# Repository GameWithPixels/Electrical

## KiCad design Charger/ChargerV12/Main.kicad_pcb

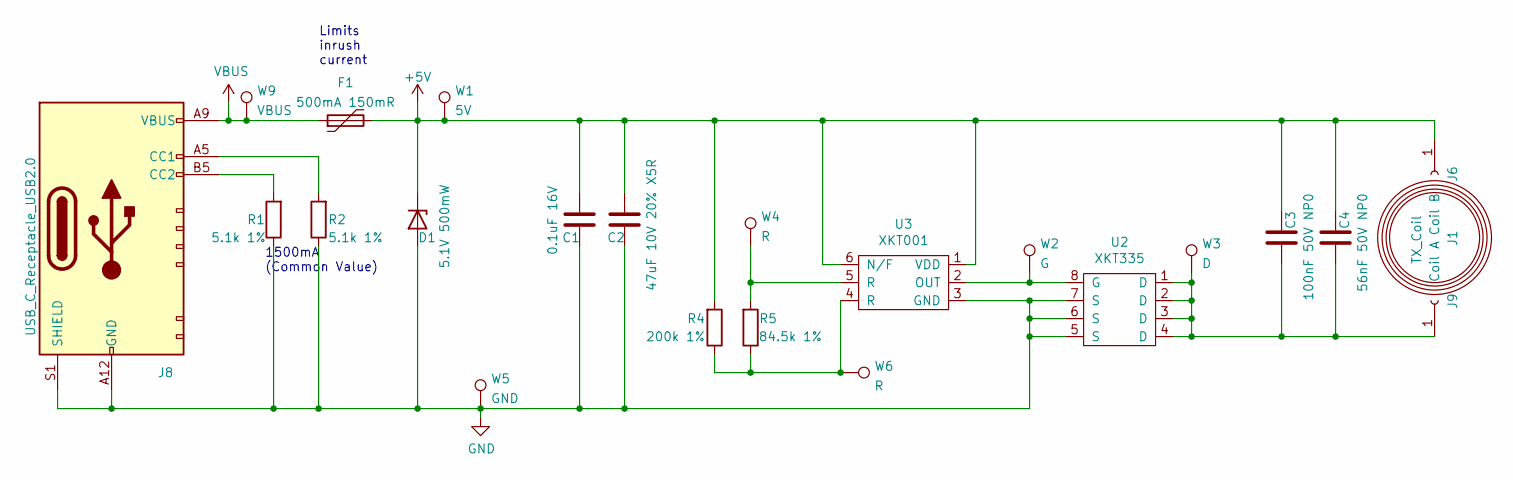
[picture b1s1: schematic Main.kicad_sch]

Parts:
C1: 0.1uF 16V; C_0603_1608Metric; Part Number CL10B104KO8NNNC; LCSC Part Number C66501
C2: 47uF 10V 20% X5R; C_1206_3216Metric; Part Number GRM31CR61A476ME15L; LCSC Part Number C94034
C3: 100nF 50V NP0; C_1206_3216Metric; Part Number GRM31C5C1H104JA01L; LCSC Part Number C21812
C4: 56nF 50V NP0; C_1206_3216Metric; Part Number GRM31M5C1H563JA01L; LCSC Part Number C441752
D1: 5.1V 500mW; D_SOD-123; Part Number BZT52C5V1; LCSC Part Number C353516
F1: 500mA 150mR; Fuse_0805_2012Metric; Part Number ASMD0805-050; LCSC Part Number C135329
J1: TX_Coil; TX Coil
J6: Coil B; TestPoint_THTPad_D2.0mm_Drill1.0mm
J8: USB_C_Receptacle_USB2.0; USB-C-SMD_10P-P1.00-L6.8-W8.9; Part Number TYPE-C-31-M-17; LCSC Part Number C283540
J9: Coil A; TestPoint_THTPad_D2.0mm_Drill1.0mm
R1, R2: 5.1k 1%; R_0402_1005Metric; Part Number 0402WGF5101TCE; LCSC Part Number C25905
R4: 200k 1%; R_0603_1608Metric; Part Number 0603WAF2003T5E; LCSC Part Number C25811
R5: 84.5k 1%; R_0603_1608Metric; Part Number 0603WAF8452T5E; LCSC Part Number C23118
U2: XKT335; SOIC-8_3.9x4.9mm_P1.27mm; Part Number XKT335
U3: XKT001; SOT-23-6; Part Number XKT001
W1: 5V; TEST_PIN
W2: G; TEST_PIN
W3: D; TEST_PIN
W4, W6: R; TEST_PIN
W5: GND; TEST_PIN
W9: VBUS; TEST_PIN

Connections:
+5V: C1.1, C2.1, C3.2, C4.2, D1.1 (K), F1.2, J6.1, R4.2, U3.1 (VDD), U3.6 (N/F), W1.1
GND: C1.2, C2.2, D1.2 (A), J8.A12 (GND), J8.B12 (GND), J8.S1 (SHIELD), R1.1, R2.1, U2.5 (S), U2.6 (S), U2.7 (S), U3.3 (GND), W5.1
unnamed: C3.1, C4.1, J9.1, U2.1 (D), U2.2 (D), U2.3 (D), U2.4 (D), W3.1
unnamed: J8.A5 (CC1), R2.2
unnamed: J8.B5 (CC2), R1.2
unnamed: R4.1, R5.1, U3.4 (R), W6.1
unnamed: R5.2, U3.5 (R), W4.1
unnamed: U2.8 (G), U3.2 (OUT), W2.1
VBUS: F1.1, J8.A9 (VBUS), J8.B9 (VBUS), W9.1

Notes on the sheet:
Limits inrush current
1500mA (Common Value)

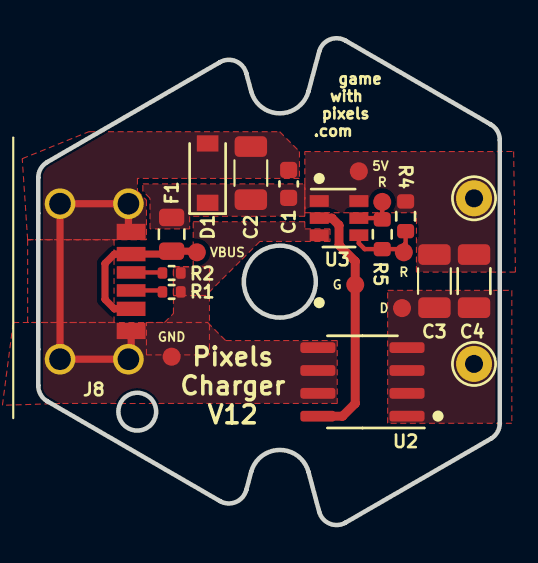
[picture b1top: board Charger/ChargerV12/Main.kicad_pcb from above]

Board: 2 copper layers, 25.6 x 27.0 mm, 23 parts (1 on the bottom side), 9 nets.

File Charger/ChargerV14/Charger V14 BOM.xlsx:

Source: | C:\Projects\Pixels-dice\Electrical\Charger\ChargerV14\Main.kicad_sch
Date: | 44894.778726851851
Item | Qty | Reference(s) | Value | Footprint | Manufacturer | Part Number
1 | 1 | C1 | 0.1uF 16V | Capacitor_SMD:C_0603_1608Metric | Samsung Electro-Mechanics | CL10B104KO8NNNC
2 | 1 | C2 | 100uF 10V 20% X5R | Capacitor_SMD:C_1206_3216Metric | Murata | GRM31CR61A107MEA8K
3 | 1 | C3 | 100nF 50V NP0 | Capacitor_SMD:C_1206_3216Metric | Murata | GRM31C5C1H104JA01L
4 | 1 | C4 | 56nF 50V NP0 | Capacitor_SMD:C_1206_3216Metric | Murata | GRM31M5C1H563JA01L
5 | 1 | D1 | D_TVS | Diode_SMD:D_0402_1005Metric | Murata | LXES1UTAA1-157
6 | 1 | F1 | 250mA 150mR | Fuse:Fuse_0805_2012Metric | Shenzhen JDT Fuse | ASMD0603-025-16V
9 | 1 | J8 | USB_C_Receptacle_USB2.0 | Pixels-dice:USB-C-SMD_10P-P1.00-L6.8-W8.9 | Korean Hroparts Elec | TYPE-C-31-M-17
11 | 2 | R1, R2 | 5.1k 1% | Resistor_SMD:R_0402_1005Metric | UNI-ROYAL(Uniroyal Elec) | 0402WGF5101TCE
12 | 1 | R4 | 200k 1% | Resistor_SMD:R_0603_1608Metric | UNI-ROYAL(Uniroyal Elec) | 0603WAF2003T5E
13 | 1 | R5 | 84.5k 1% | Resistor_SMD:R_0603_1608Metric | UNI-ROYAL(Uniroyal Elec) | 0603WAF8452T5E
14 | 1 | U2 | XKT335 | Pixels-dice:SOIC-8_3.9x4.9mm_P1.27mm | XKT | XKT335
15 | 1 | U3 | XKT001 | Package_TO_SOT_SMD:SOT-23-6 | XKT | XKT001

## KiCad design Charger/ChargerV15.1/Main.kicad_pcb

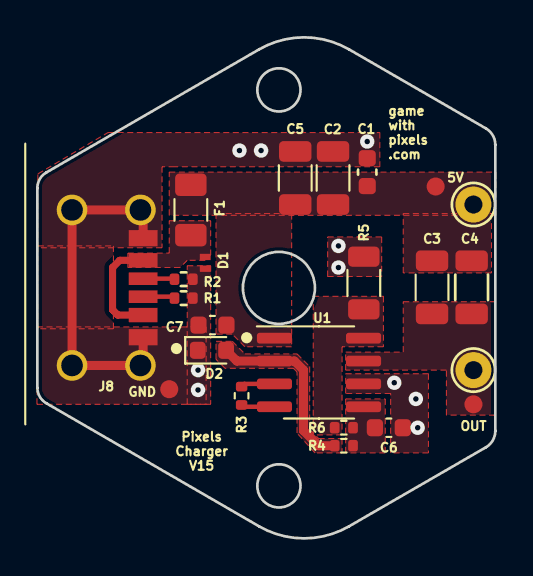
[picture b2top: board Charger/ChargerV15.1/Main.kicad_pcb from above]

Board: 2 copper layers, 25.4 x 27.8 mm, 24 parts (1 on the bottom side), 11 nets.

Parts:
C1, C6, C7: 0.1uF 16V; C_0603_1608Metric
C2, C5: 47uF 10V 20% X5R; C_1206_3216Metric
C3: 100nF 50V NP0; C_1206_3216Metric
C4: 56nF 50V NP0; C_1206_3216Metric
D1: D_TVS; DFN
D2: LED; LED_0603_1608Metric
F1: 250mA 150mR; Fuse_1206_3216Metric
J1: TX_Coil; TX Coil
J6: Coil B; TestPoint_THTPad_D2.0mm_Drill1.0mm
J8: USB_C_Receptacle_USB2.0; USB-C-SMD_10P-P1.00-L6.8-W8.9
J9: Coil A; TestPoint_THTPad_D2.0mm_Drill1.0mm
R1, R2: 5.1k 1%; R_0402_1005Metric
R3: 250k 1%; R_0402_1005Metric
R4: 120k 1%; R_0402_1005Metric
R5: 0.4R; R_1206_3216Metric
R6: 1.5k 1%; R_0402_1005Metric
U1: XKT520; SOIC-8_3.9x4.9mm_P1.27mm
W1: 5V; TEST_PIN
W5: GND; TEST_PIN
W6: OUT; TEST_PIN

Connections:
+5V: C1.1, C2.1, C3.2, C4.2, C5.1, C7.1, F1.2, J6.1, U1.1 (VDD), W1.1
GND: C1.2, C2.2, C5.2, C6.1, C7.2, D1.2 (A2), D2.1 (K), J8.A12 (GND), J8.B12 (GND), J8.S1 (SHIELD), R1.1, R2.1, R5.1, U1.6 (VSS), W5.1
GNDPWR: R5.2, R6.2, U1.8 (PVSS)
unnamed: C3.1, C4.1, J9.1, U1.7 (OUT), W6.1
unnamed: C6.2, R4.1, R6.1, U1.5 (FB)
unnamed: D2.2 (A), R4.2, U1.2 (LED)
unnamed: J8.A5 (CC1), R2.2
unnamed: J8.B5 (CC2), R1.2
unnamed: R3.1, U1.4 (R)
unnamed: R3.2, U1.3 (R)
VBUS: D1.1 (A1), F1.1, J8.A9 (VBUS), J8.B9 (VBUS)

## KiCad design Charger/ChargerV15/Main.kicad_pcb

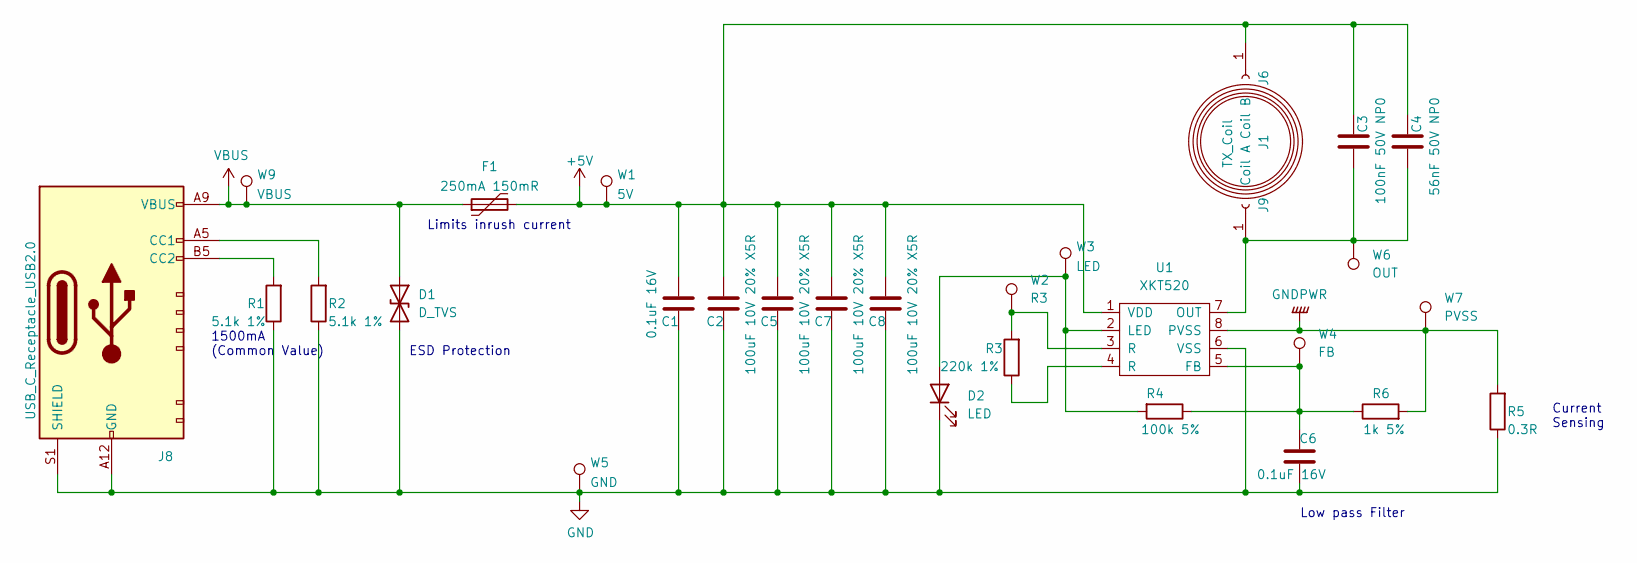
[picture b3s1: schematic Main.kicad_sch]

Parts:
C1, C6: 0.1uF 16V; C_0603_1608Metric; Part Number CL10B104KO8NNNC; LCSC Part Number C66501
C2, C5, C7, C8: 100uF 10V 20% X5R; C_1206_3216Metric; Part Number GRM31CR61A107ME05L; LCSC Part Number C312983
C3: 100nF 50V NP0; C_1206_3216Metric; Part Number GRM31C5C1H104JA01L; LCSC Part Number C21812
C4: 56nF 50V NP0; C_1206_3216Metric; Part Number GRM31M5C1H563JA01L; LCSC Part Number C441752
D1: D_TVS; DFN; Part Number LXES1UTAA1-157; LCSC Part Number C5210979
D2: LED; LED_0603_1608Metric; Part Number XL-1606SURC; LCSC Part Number C965860
F1: 250mA 150mR; Fuse_1206_3216Metric; Part Number BSMD1206-025-33V; LCSC Part Number C2977524
J1: TX_Coil; TX Coil
J6: Coil B; TestPoint_THTPad_D2.0mm_Drill1.0mm
J8: USB_C_Receptacle_USB2.0; USB-C-SMD_10P-P1.00-L6.8-W8.9; Part Number TYPE-C-31-M-17; LCSC Part Number C283540
J9: Coil A; TestPoint_THTPad_D2.0mm_Drill1.0mm
R1, R2: 5.1k 1%; R_0402_1005Metric; Part Number 0402WGF5101TCE; LCSC Part Number C25905
R3: 220k 1%; R_0402_1005Metric; Part Number 0402WGF2203TCE; LCSC Part Number C25767
R4: 100k 5%; R_0402_1005Metric; Part Number 0402WGF1003TCE; LCSC Part Number C25741
R5: 0.3R; R_1206_3216Metric; Part Number RL1206JR-070R3L; LCSC Part Number C327153
R6: 1k 5%; R_0402_1005Metric; Part Number 0402WGJ0102TCE; LCSC Part Number C25543
U1: XKT520; SOIC-8_3.9x4.9mm_P1.27mm
W1: 5V; TEST_PIN
W2: R3; TEST_PIN
W3: LED; TEST_PIN
W4: FB; TEST_PIN
W5: GND; TEST_PIN
W6: OUT; TEST_PIN
W7: PVSS; TEST_PIN
W9: VBUS; TEST_PIN

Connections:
+5V: C1.1, C2.1, C3.2, C4.2, C5.1, C7.1, C8.1, F1.2, J6.1, U1.1 (VDD), W1.1
GND: C1.2, C2.2, C5.2, C6.1, C7.2, C8.2, D1.2 (A2), D2.1 (K), J8.A12 (GND), J8.B12 (GND), J8.S1 (SHIELD), R1.1, R2.1, R5.1, U1.6 (VSS), W5.1
GNDPWR: R5.2, R6.2, U1.8 (PVSS), W7.1
unnamed: C3.1, C4.1, J9.1, U1.7 (OUT), W6.1
unnamed: C6.2, R4.1, R6.1, U1.5 (FB), W4.1
unnamed: D2.2 (A), R4.2, U1.2 (LED), W3.1
unnamed: J8.A5 (CC1), R2.2
unnamed: J8.B5 (CC2), R1.2
unnamed: R3.1, U1.4 (R)
unnamed: R3.2, U1.3 (R), W2.1
VBUS: D1.1 (A1), F1.1, J8.A9 (VBUS), J8.B9 (VBUS), W9.1

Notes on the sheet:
ESD Protection
Current Sensing
Low pass Filter
Limits inrush current
1500mA (Common Value)

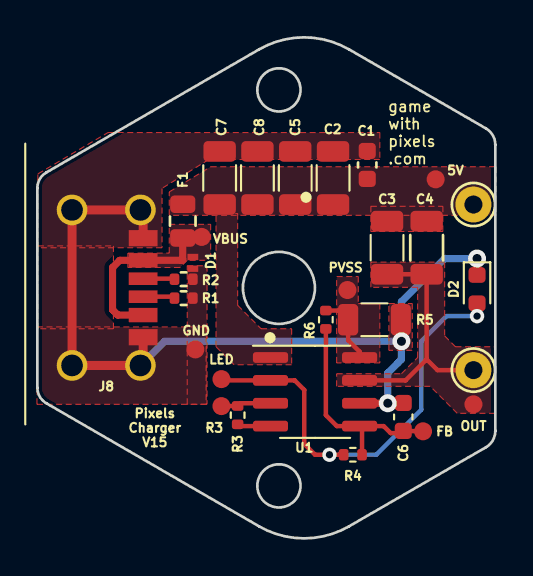
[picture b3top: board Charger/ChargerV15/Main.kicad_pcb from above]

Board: 2 copper layers, 25.4 x 27.8 mm, 30 parts (1 on the bottom side), 11 nets.

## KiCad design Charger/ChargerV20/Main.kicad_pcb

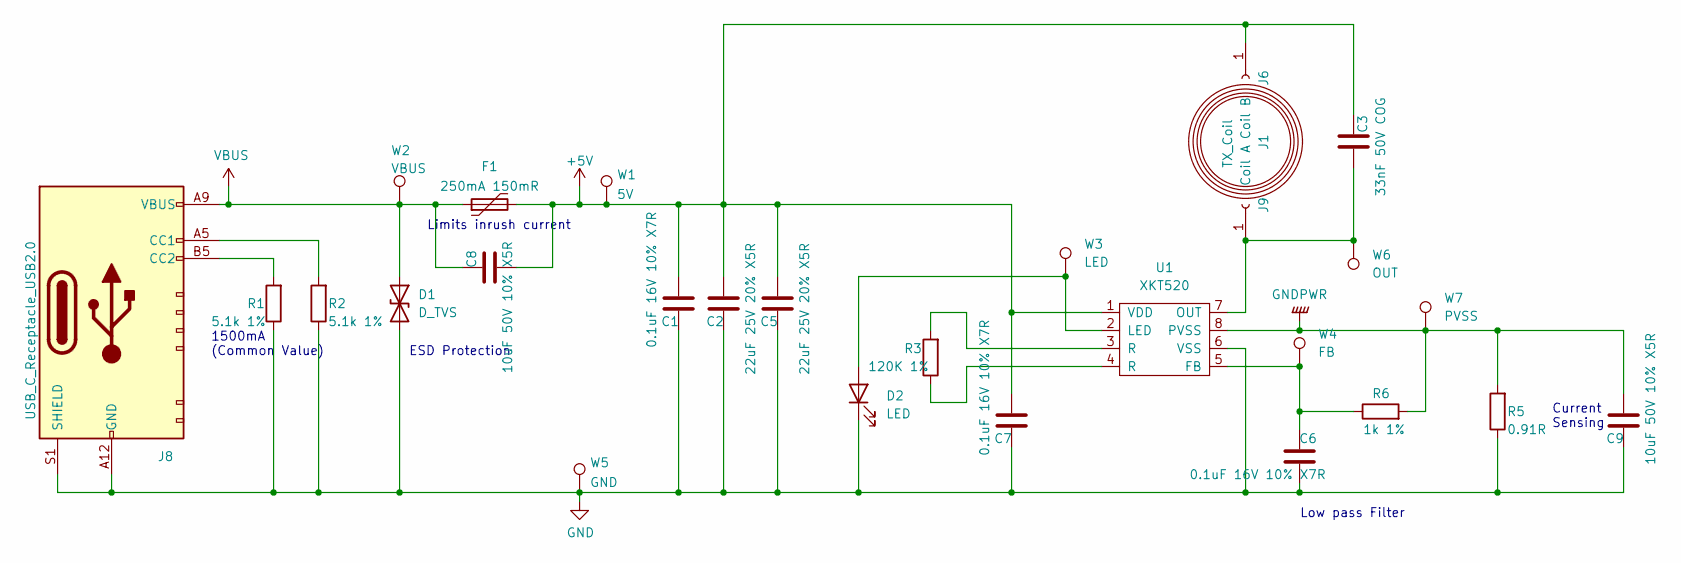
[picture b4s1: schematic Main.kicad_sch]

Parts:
C1, C6, C7: 0.1uF 16V 10% X7R; C_0603_1608Metric; Part Number CL10B104KO8NNNC; LCSC Part Number C66501
C2, C5: 22uF 25V 20% X5R; C_0805_2012Metric; Part Number GRM21BR61E226ME44L; LCSC Part Number C86816
C3: 33nF 50V COG; C_1206_3216Metric; Part Number GRM31C5C1H104JA01L; LCSC Part Number C97946
C8: 10uF 50V 10% X5R; C_0805_2012Metric; Part Number GRM21BR61H106KE43L; LCSC Part Number C440198
C9: 10uF 50V 10% X5R; C_0805_2012Metric; Part Number GRM21BR61H106KE43L
D1: D_TVS; DFN; Part Number LXES1UTAA1-157; LCSC Part Number C5210979
D2: LED; LED_0603_1608Metric; Part Number LTST-C191KRKT; LCSC Part Number C125099
F1: 250mA 150mR; Fuse_1206_3216Metric; Part Number BSMD1206-025-33V; LCSC Part Number C2977524
J1: TX_Coil; TX Coil
J6: Coil B; TestPoint_Pad_D2.0mm_V1.1
J8: USB_C_Receptacle_USB2.0; USB-C-SMD_10P-P1.00-L6.8-W8.9_V1.1; Part Number TYPE-C-31-M-17; LCSC Part Number C283540
J9: Coil A; TestPoint_Pad_D2.0mm_V1.1
R1, R2: 5.1k 1%; R_0402_1005Metric; Part Number 0402WGF5101TCE; LCSC Part Number C25905
R3: 120K 1%; R_0402_1005Metric; Part Number 0402WGF2003TCE; LCSC Part Number C25764
R5: 0.91R; R_1206_3216Metric; Part Number RL1206FR-070R3L; LCSC Part Number C705562
R6: 1k 1%; R_0402_1005Metric; Part Number 0402WGF1501TCE; LCSC Part Number C25867
U1: XKT520; SOIC-8_3.9x4.9mm_P1.27mm
W1: 5V; TEST_PIN1.5MM
W2: VBUS; TEST_PIN1.5MM
W3: LED; TEST_PIN1.5MM
W4: FB; TEST_PIN1.5MM
W5: GND; TEST_PIN1.5MM
W6: OUT; TEST_PIN1.5MM
W7: PVSS; TEST_PIN1.5MM

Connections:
+5V: C1.1, C2.1, C3.2, C5.1, C7.1, C8.1, F1.2, J6.1, U1.1 (VDD), W1.1
GND: C1.2, C2.2, C5.2, C6.1, C7.2, C9.2, D1.2 (A2), D2.1 (K), J8.A12 (GND), J8.B12 (GND), J8.S1 (SHIELD), R1.1, R2.1, R5.1, U1.6 (VSS), W5.1
GNDPWR: C9.1, R5.2, R6.2, U1.8 (PVSS), W7.1
unnamed: C3.1, J9.1, U1.7 (OUT), W6.1
unnamed: C6.2, R6.1, U1.5 (FB), W4.1
unnamed: D2.2 (A), U1.2 (LED), W3.1
unnamed: J8.A5 (CC1), R2.2
unnamed: J8.B5 (CC2), R1.2
unnamed: R3.1, U1.4 (R)
unnamed: R3.2, U1.3 (R)
VBUS: C8.2, D1.1 (A1), F1.1, J8.A9 (VBUS), J8.B9 (VBUS), W2.1

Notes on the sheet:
ESD Protection
Current Sensing
Low pass Filter
Limits inrush current
1500mA (Common Value)

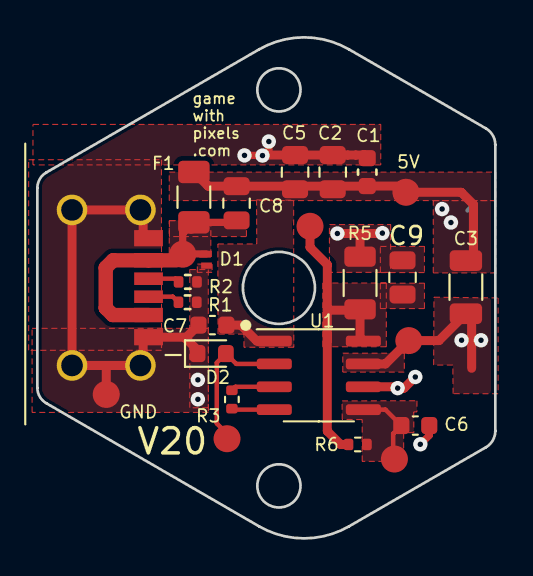
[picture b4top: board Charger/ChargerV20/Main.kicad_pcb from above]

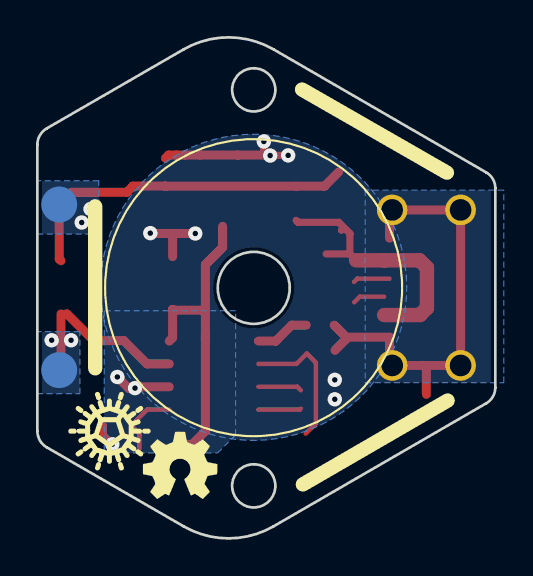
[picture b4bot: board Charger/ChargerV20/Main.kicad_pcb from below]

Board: 2 copper layers, 25.4 x 27.8 mm, 28 parts (3 on the bottom side), 11 nets.

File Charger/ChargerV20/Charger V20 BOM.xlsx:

Comment | Designator | Footprint | JLCPCB Part #（optional）
0.1uF 16V 10% X7R | C1, C6, C7 | Capacitor_SMD:C_0603_1608Metric | C66501
22uF 25V 20% X5R | C2, C5 | Capacitor_SMD:C_0805_2012Metric | C86816
33nF 50V COG | C3 | Capacitor_SMD:C_1206_3216Metric
10uF 50V 10% X5R | C8, C9 | Capacitor_SMD:C_0805_2012Metric | C440198
D_TVS | D1 | Pixels-dice:DFN | C5210979
LED | D2 | LED_SMD:LED_0603_1608Metric | C125099
250mA 150mR | F1 | Fuse:Fuse_1206_3216Metric | C2977524
USB_C_Receptacle_USB2.0 | J8 | Pixels-dice:USB-C-SMD_10P-P1.00-L6.8-W8.9_V1.1 | C283540
5.1k 1% | R1, R2 | Resistor_SMD:R_0402_1005Metric | C25905
120K 1% | R3 | Resistor_SMD:R_0402_1005Metric | C25750
0.91R | R5 | Resistor_SMD:R_1206_3216Metric | C136987
1k 1% | R6 | Resistor_SMD:R_0402_1005Metric | C11702
XKT520 | U1 | Pixels-dice:SOIC-8_3.9x4.9mm_P1.27mm

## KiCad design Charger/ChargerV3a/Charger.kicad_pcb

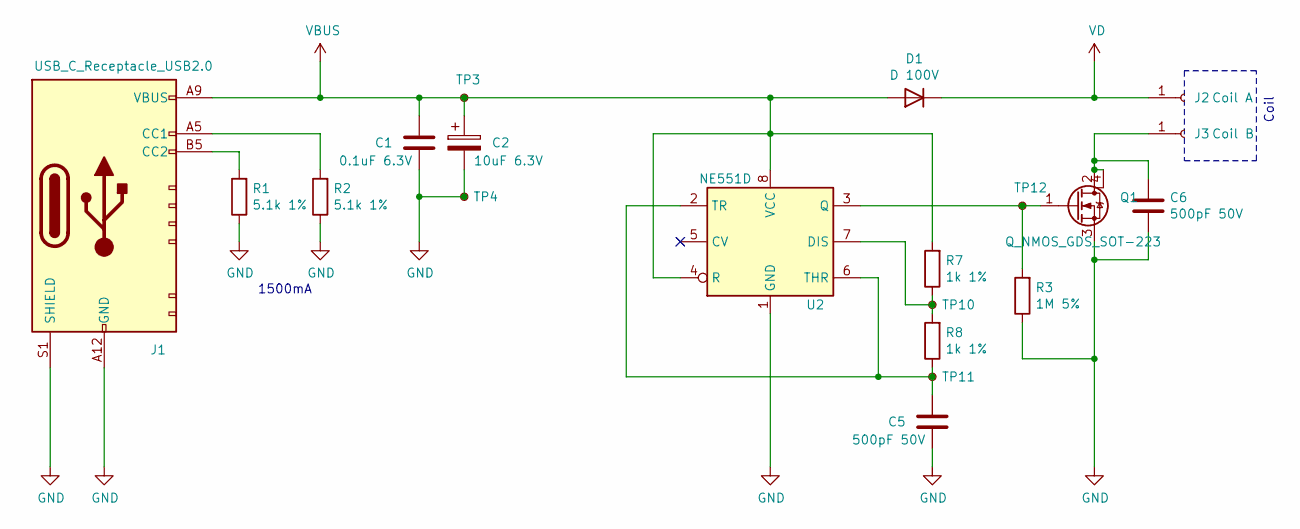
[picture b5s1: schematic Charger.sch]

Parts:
C1: 0.1uF 6.3V; C_0603_1608Metric; Part Number TCC0603X7R104K500CT; LCSC Part Number C282519
C2: 10uF 6.3V; C_0603_1608Metric; Part Number CL10A106MP8NNNC; LCSC Part Number C85713
C5, C6: 500pF 50V; C_0805_2012Metric; Part Number CC0805KRX7R0BB471; LCSC Part Number C107138
D1: D 100V; D_SOD-123F; Part Number DSS210; LCSC Part Number C511868
J1: USB_C_Receptacle_USB2.0; USB-C-SMD_10P-P1.00-L6.8-W8.9; Part Number TYPE-C-31-M-17; LCSC Part Number C283540
J2: Coil A; TestPoint_THTPad_D2.0mm_Drill1.0mm
J3: Coil B; TestPoint_THTPad_D2.0mm_Drill1.0mm
Q1: Q_NMOS_GDS_SOT-223; SOT-223; Part Number HSL0004; LCSC Part Number C508454
R1, R2: 5.1k 1%; R_0603_1608Metric; Part Number WR06X5101FTL; LCSC Part Number C113390
R3: 1M 5%; R_0603_1608Metric; Part Number 0603WAJ0105T5E; LCSC Part Number C26098
R7, R8: 1k 1%; R_0603_1608Metric; Part Number 0603WAF1001T5E; LCSC Part Number C21190
TP3, TP4, TP10, TP11, TP12: TestPoint_Small; TestPoint_Pad_1.0x1.0mm
U2: NE551D; SOP-8_3.9x4.9mm_P1.27mm; Part Number XL551; LCSC Part Number C707074

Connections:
GND: C1.2, C2.2, C5.2, C6.2, J1.A12 (GND), J1.B12 (GND), J1.S1 (SHIELD), Q1.3 (S), R1.1, R2.1, R3.1, TP4.1, U2.1 (GND)
unnamed: C5.1, R8.1, TP11.1, U2.2 (TR), U2.6 (THR)
unnamed: C6.1, J3.1, Q1.2 (D), Q1.4
unnamed: J1.A5 (CC1), R2.2
unnamed: J1.B5 (CC2), R1.2
unnamed: Q1.1 (G), R3.2, TP12.1, U2.3 (Q)
unnamed: R7.1, R8.2, TP10.1, U2.7 (DIS)
VBUS: C1.1, C2.1, D1.2 (A), J1.A9 (VBUS), J1.B9 (VBUS), R7.2, TP3.1, U2.4 (R), U2.8 (VCC)
VD: D1.1 (K), J2.1

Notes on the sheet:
1500mA
Coil

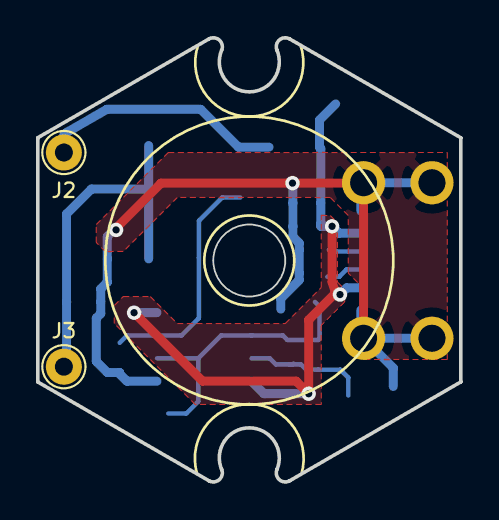
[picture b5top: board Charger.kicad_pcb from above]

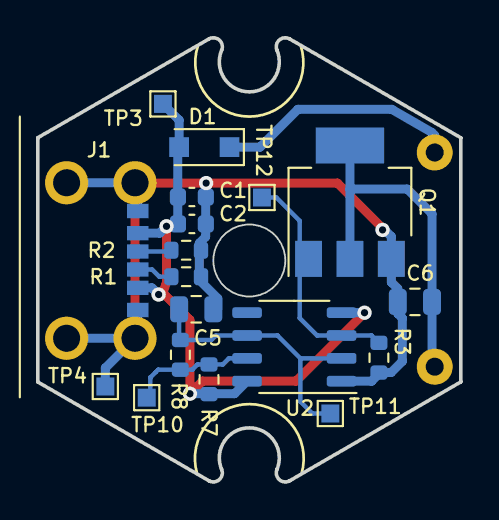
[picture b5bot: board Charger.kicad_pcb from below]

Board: 2 copper layers, 23.5 x 24.7 mm, 20 parts (18 on the bottom side), 9 nets.
